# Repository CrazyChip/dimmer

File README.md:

dimmer
======

* 8 channel dimmer
* DIN rail box
* analog (0..10V) and RS485 interfaces

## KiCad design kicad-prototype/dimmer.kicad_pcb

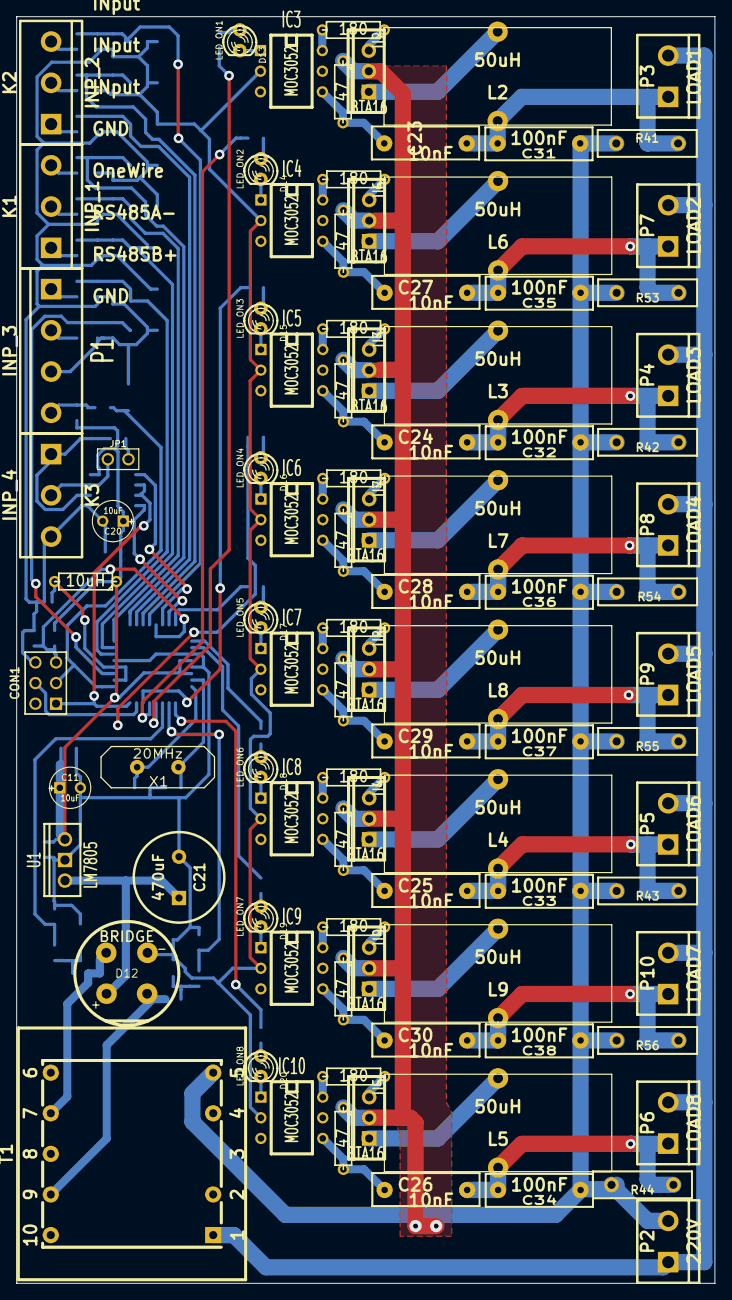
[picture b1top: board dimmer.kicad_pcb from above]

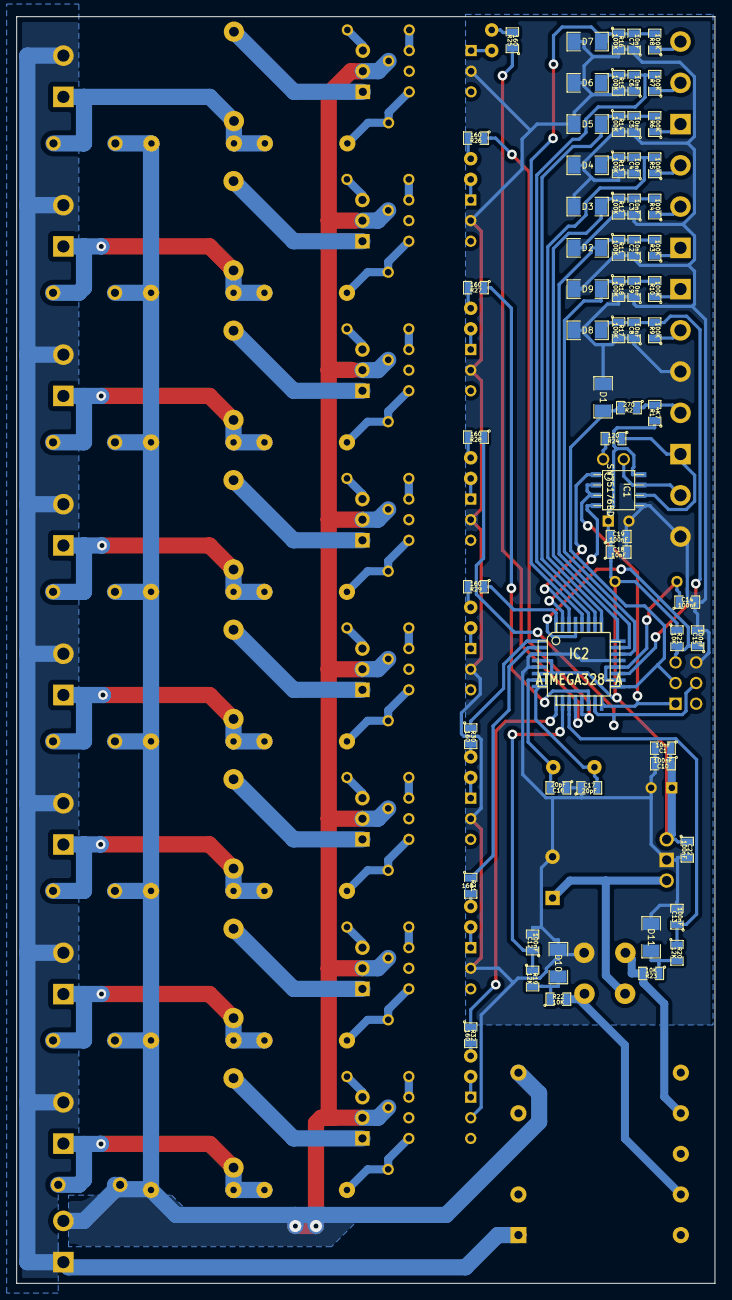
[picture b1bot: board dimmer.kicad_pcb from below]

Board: 2 copper layers, 86.0 x 156.0 mm, 159 parts (64 on the bottom side), 103 nets.

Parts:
C1, C2, C3, C4, C5, C6, C7, C8, C9, C18: 10nF; SM0805
C10, C12, C13, C14, C15, C19, C22: 100nF; SM0805
C11, C20: 10uF; C1V5
C16, C17: 20pF; SM0805
C21: 470uF; C2V10
C23, C24, C25, C26, C27, C28, C29, C30: 10nF; cnp_13x4mm
C31, C32, C33, C34, C35, C36, C37, C38: 100nF; cnp_13x4mm
CON1: AVR-ISP-6; pin_array_3x2
D1, D2, D3, D4, D5, D6, D7, D8, D9: 5.1V; SM1206
D10, D11: BYV10-40; SM1206
D12: BRIDGE; PUSH_BUTT_SHAPE1
D13: LED_ON1; LED-3MM
D14: LED_ON2; LED-3MM
D15: LED_ON3; LED-3MM
D16: LED_ON4; LED-3MM
D17: LED_ON5; LED-3MM
D18: LED_ON6; LED-3MM
D19: LED_ON7; LED-3MM
D20: LED_ON8; LED-3MM
IC1: SN75176BD; so-8
IC2: ATMEGA328-A; TQFP32
IC3, IC4, IC5, IC6, IC7, IC8, IC9, IC10: MOC3052; DIP-6__300
JP1: JUMPER; PIN_ARRAY_2X1
K1: INP_1; bornier3
K2: INP_2; bornier3
K3: INP_4; bornier3
L1: 10uH; R3
L2, L3, L4, L5, L6, L7, L8, L9: 50uH; droselis27x12
P1: INP_3; bornier4
P2: 220V; bornier2
P3: LOAD1; bornier2
P4: LOAD3; bornier2
P5: LOAD6; bornier2
P6: LOAD8; bornier2
P7: LOAD2; bornier2
P8: LOAD4; bornier2
P9: LOAD5; bornier2
P10: LOAD7; bornier2
R1: 4K7; SM0805
R2: 270; SM0805
R3, R4, R5, R6, R7, R8, R9, R10, R11, R12, R13, R14, R15, R16, R17, R18: 100K; SM0805
R19, R20: 12K; SM0805
R21, R22, R23: 10K; SM0805
R24: 120; SM0805
R25, R26, R27, R28, R29, R30, R31, R32: 160; SM0805
R33, R34, R35, R36, R45, R46, R47, R48: 180; R3
R37, R38, R39, R40, R49, R50, R51, R52: 47; R3
R41, R42, R43, R44, R53, R54, R55, R56: RVAR; cnp_12mm_disc
T1: TRANSFO; TEZ-28x33
U1: LM7805; LM78XXV
U2, U3, U4, U5, U6, U7, U8, U9: BTA16; TO220_VERT_123
X1: 20MHz; HC-18UV

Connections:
220_L: C31.1, C32.1, C33.1, C34.1, C35.1, C36.1, C37.1, C38.1, P2.2, R37.1, R38.1, R39.1, R40.1, R41.1, R42.1, R43.1, R44.1, R49.1, R50.1, R51.1, R52.1, R53.1, R54.1, R55.1, R56.1, T1.5, U2.2, U3.2, U4.2, U5.2, U6.2, U7.2, U8.2, U9.2
220_N: P2.1, P3.2, P4.2, P5.2, P6.2, P7.2, P8.2, P9.2, P10.2, T1.1
+5V: C1.1, C10.1, C11.1, C18.1, C19.1, C20.1, C22.1, IC1.8, IC2.4, IC2.6, L1.1, R1.1, R21.1, U1.VO
ADC0: C2.2, D2.2, IC2.23, R3.2, R11.1
ADC1: C3.2, D3.2, IC2.24, R4.2, R12.1
ADC2: C4.2, D4.2, IC2.25, R5.2, R13.1
ADC3: C5.2, D5.2, IC2.26, R6.2, R14.1
ADC4: C6.2, D6.2, IC2.27, R7.2, R15.1
ADC5: C7.2, D7.2, IC2.28, R8.2, R16.1
ADC6: C8.2, D8.2, IC2.19, R9.2, R17.1
ADC7: C9.2, D9.2, IC2.22, R10.2, R18.1
AIN0: C12.1, IC2.10, R19.1
AIN1: C13.1, IC2.11, R20.1
DI: IC1.4, IC2.31
GND: C1.2, C2.1, C3.1, C4.1, C5.1, C6.1, C7.1, C8.1, C9.1, C10.2, C11.2, C12.2, C13.2, C14.2, C15.2, C16.1, C17.1, C18.2, C19.2, C20.2, C21.2, C22.2, CON1.6, D1.1, D2.1, D3.1, D4.1, D5.1, D6.1, D7.1, D8.1, D9.1, D10.2, D11.2, D12.1, IC1.5, IC2.3, IC2.5, IC2.21, IC3.2, IC4.2, IC5.2, IC6.2, IC7.2, IC8.2, IC9.2, IC10.2, K3.3, P1.3, R11.2, R12.2, R13.2, R14.2, R15.2, R16.2, R17.2, R18.2, U1.GND
IN_1WIRE: P1.4, R1.2, R2.1
MISO: CON1.1, IC1.2, IC1.3, IC2.16
MOSI: CON1.4, IC2.15, R28.1
unnamed: L3.1, U3.1
unnamed: IC3.6, R33.2
unnamed: R33.1, U2.3
unnamed: C23.1, IC3.4, R37.2
unnamed: R34.1, U3.3
unnamed: IC5.6, R34.2
unnamed: C24.1, IC5.4, R38.2
unnamed: D19.2, IC9.1
unnamed: D17.1, R29.2
unnamed: D18.1, R30.2
unnamed: D19.1, R31.2
unnamed: D20.1, R32.2
unnamed: C21.1, D12.3, U1.VI
unnamed: L5.1, U5.1
unnamed: IC8.6, R35.2
unnamed: R35.1, U4.3
unnamed: C25.1, IC8.4, R39.2
unnamed: R36.1, U5.3
unnamed: C26.2, C34.2, L5.2, P6.1, R44.2
unnamed: C26.1, IC10.4, R40.2
unnamed: L4.1, U4.1
unnamed: D20.2, IC10.1
unnamed: C14.1, IC2.18, IC2.20, L1.2
unnamed: K1.3, R5.1
unnamed: K2.1, R6.1
unnamed: K2.2, R7.1
unnamed: K2.3, R8.1
unnamed: P1.1, R10.1
unnamed: D10.1, R19.2, R22.1
unnamed: D11.1, R20.2, R23.1
unnamed: IC1.6, K3.1, R24.1
unnamed: D12.2, R23.2, T1.7
unnamed: D13.1, R25.2
unnamed: D14.1, R26.2
unnamed: D15.1, R27.2
unnamed: D15.2, IC5.1
unnamed: D16.2, IC6.1
unnamed: D16.1, R28.2
unnamed: D13.2, IC3.1
unnamed: D17.2, IC7.1
unnamed: D18.2, IC8.1
unnamed: D14.2, IC4.1
unnamed: JP1.2, R24.2
unnamed: IC1.7, JP1.1, K3.2
unnamed: D12.4, R22.2, T1.9
unnamed: IC7.6, R47.2
unnamed: IC9.6, R48.2
unnamed: L2.1, U2.1
unnamed: L6.1, U6.1
unnamed: R48.1, U9.3
unnamed: C30.1, IC9.4, R52.2
unnamed: IC10.6, R36.2
unnamed: IC4.6, R45.2
unnamed: L7.1, U7.1
unnamed: L9.1, U9.1
unnamed: P1.2, R9.1
unnamed: C25.2, C33.2, L4.2, P5.1, R43.2
unnamed: C24.2, C32.2, L3.2, P4.1, R42.2
unnamed: L8.1, U8.1
unnamed: R45.1, U6.3
unnamed: C27.1, IC4.4, R49.2
unnamed: R46.1, U7.3
unnamed: IC6.6, R46.2
unnamed: C28.2, C36.2, L7.2, P8.1, R54.2
unnamed: C28.1, IC6.4, R50.2
unnamed: C27.2, C35.2, L6.2, P7.1, R53.2
unnamed: R47.1, U8.3
unnamed: C29.1, IC7.4, R51.2
unnamed: C30.2, C38.2, L9.2, P10.1, R56.2
unnamed: C29.2, C37.2, L8.2, P9.1, R55.2
unnamed: C16.2, IC2.7, X1.1
unnamed: C17.2, IC2.8, X1.3
unnamed: C23.2, C31.2, L2.2, P3.1, R41.2
unnamed: K1.2, R4.1
unnamed: IC2.12, R25.1
unnamed: IC2.13, R26.1
unnamed: IC2.14, R27.1
unnamed: IC2.32, R29.1
unnamed: IC2.1, R30.1
unnamed: IC2.2, R31.1
unnamed: IC2.9, R32.1
unnamed: K1.1, R3.1
RESET: C15.1, CON1.5, IC2.29, R21.2
RO: IC1.1, IC2.30
SCK: CON1.3, D1.2, IC2.17, R2.2

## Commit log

2014-08-18 kicad project added
2014-08-18 schematic and gerbers added
2014-08-18 change in schematic
